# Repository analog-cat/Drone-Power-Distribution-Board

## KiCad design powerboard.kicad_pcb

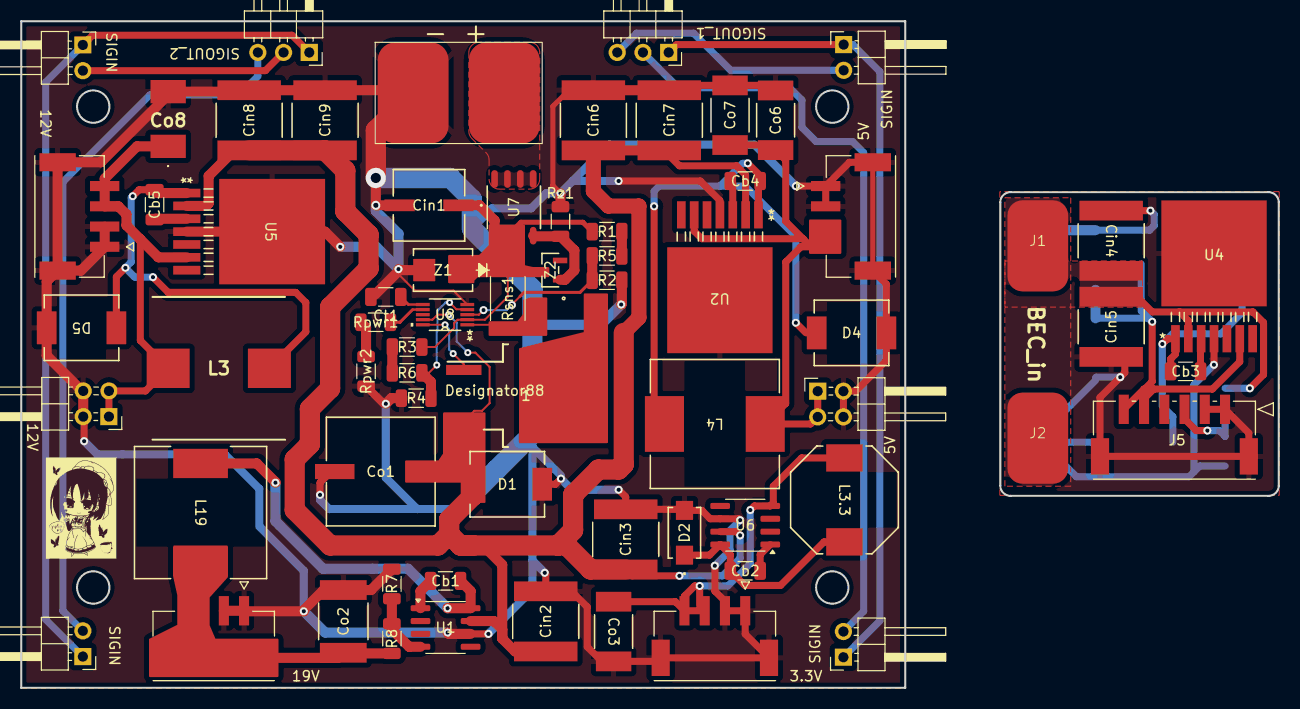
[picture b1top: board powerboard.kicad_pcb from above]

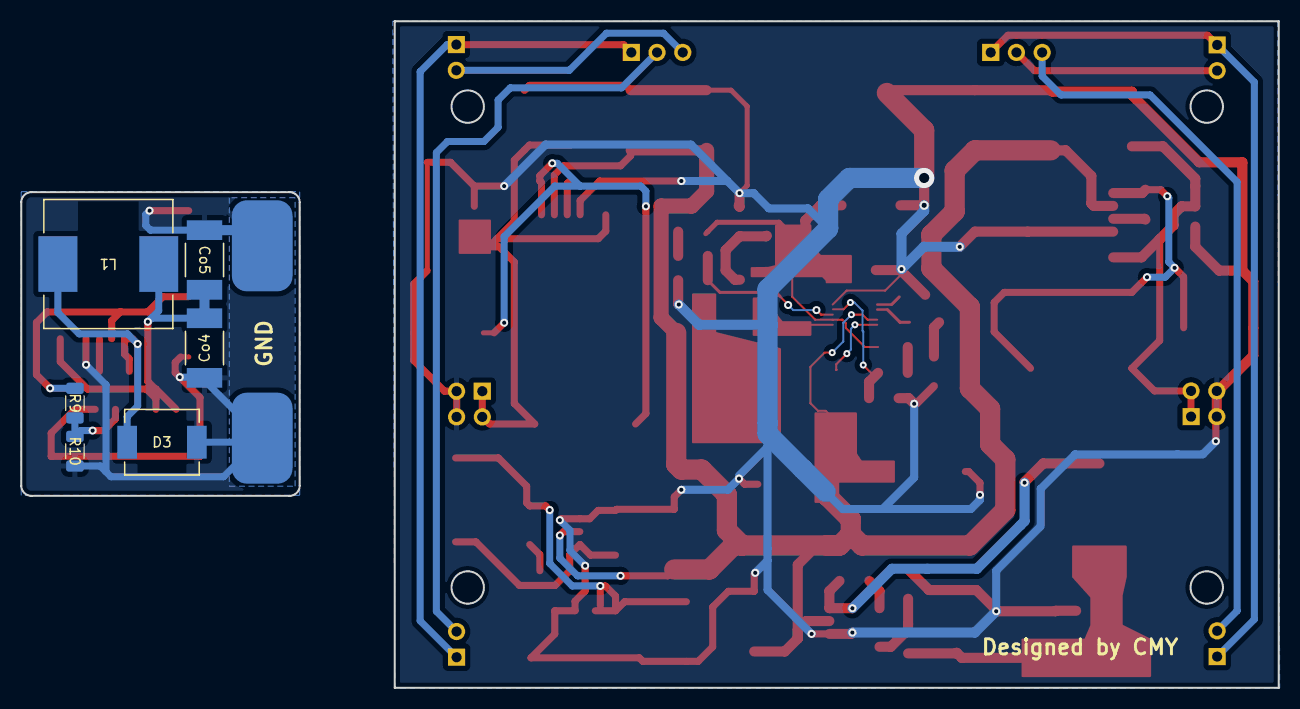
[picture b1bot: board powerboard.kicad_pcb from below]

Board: 2 copper layers, 124.2 x 65.8 mm, 73 parts (6 on the bottom side), 39 nets.

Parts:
1: CSD19536KTTT; KTT0002A
3.3V, 5V, 12V, 19V: 5024430470; MOLEX_5024430470
5V#2, 12V#2: Conn_01x04_Pin; PinHeader_2x02_P2.54mm_Horizontal
Cb1, Cb2, Cb3, Cb4, Cb5: 0.01u; C_1206_3216Metric
Cin1: 120u; CAP_ZKU_D8_PAN
Cin2, Cin3, Cin4, Cin5, Cin6, Cin7, Cin8, Cin9: 15u; CAP_594D-R_VSS
Co1: 330u; CAP_EEH_G_PAN
Co2: 33u; CAP_594D-D_VSS
Co3, Co4, Co5, Co6, Co7: 68u; CAP_594D-C_VSS
Co8: 100u; 594D107X9016C2T
Ct1: 150n; C_1206_3216Metric
D1: SS310; CR_SS310_TWS
D2: SS14; CR_SMA_403AE_OSI
D3, D4, D5: SK33; CR_SS310_TWS
J1, J2: Header2; BEC_io
J5: 5024430670; CON_5024430670
J12: Header2; Vin
L1, L4: DR125-330-R; DR125
L3: HC9-470-R; INDPM131141X750N
L3.3: 68u; IND_B82464G4_EPC
L19: 68u; IND_BOURNS_SRR1260
R1, R3: 36k; R_1206_3216Metric
R2: 8.2k; R_1206_3216Metric
R4: 4.02k; R_1206_3216Metric
R5, R6: 2k; R_1206_3216Metric
R7: 1k; R_1206_3216Metric
R8: 14.7k; R_1206_3216Metric
R9: 9.1M; R_1206_3216Metric
R10: 1M; R_1206_3216Metric
Rpwr1: 150k; R_1206_3216Metric
Rpwr2: 2k; R_1206_3216Metric
Rsns1: 6m; R_2512_6332Metric
Rz1: 1.8k; R_1206_3216Metric
SIGIN: Conn_01x02; PinHeader_1x02_P2.54mm_Horizontal
SIGIN#2, SIGIN#3, SIGIN#4: Conn_01x02; PinHeader_1x02_P2.54mm_Horizontal
SIGOUT_1, SIGOUT_2: Conn_01x03; PinHeader_1x03_P2.54mm_Horizontal
U1: LM2675M-ADJ; SOIC-8_3.9x4.9mm_P1.27mm
U2, U4: LM2676SX-5.0/NOPB; TS7B
U5: LM2676SX-12/NOPB; TS7B
U6: LM2675M-3.3; SOIC-8_3.9x4.9mm_P1.27mm
U7: FDS4435BZ; SO-8L-NB_FAS
U8: LM5069MM-2/NOPB; MUB10A
Z1: SMBJ30A; SMB_DIO
Z2: BZX84C12LT1G; SOT-23_ONS

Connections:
/1OUT: SIGIN.2, SIGOUT_1.2
/3OUT: SIGIN#3.2, SIGOUT_1.3
BEC_in: Cin4.1, Cin5.1, J1.1 (A), J2.1 (A), R9.1, U4.2 (IN)
GND: 3.3V.1, 3.3V.2, 3.3V.S1 (SHIELD1), 3.3V.S2 (SHIELD2), 5V.1, 5V.2, 5V.S1 (SHIELD1), 5V.S2 (SHIELD2), 5V#2.2, 5V#2.4, 12V.1, 12V.2, 12V.S1 (SHIELD1), 12V.S2 (SHIELD2), 12V#2.2, 12V#2.4, 19V.1, 19V.2, Cin1.2, Cin2.2, Cin3.2, Cin6.2, Cin7.2, Cin8.2, Cin9.2, Co1.2, Co2.2, Co3.2, Co6.2, Co7.2, Co8.2, Ct1.2, D1.2, D2.2 (A), D4.2 (A), D5.2 (A), J12.2 (B), R2.1, R4.1, R7.1, Rpwr2.1, Rz1.2, U1.6 (GND), U2.4 (GND), U2.8 (TAB), U5.4 (GND), U5.8 (TAB), U6.6 (GND), U8.5 (GND), Z1.2
GND_1: Cin4.2, Cin5.2, Co4.2, Co5.2, D3.2 (A), J1.2 (B), J2.2 (B), J5.1, J5.2, J5.7, J5.8, R10.2, U4.4 (GND), U4.8 (TAB)
unnamed: 1.2 (Drain), Rsns1.2, U8.1 (SEN)
unnamed: 1.1 (Gate), U8.10 (GATE)
unnamed: SIGIN.1, SIGIN#3.1, SIGOUT_1.1
unnamed: Cb2.2, D2.1 (K), L3.3.2, U6.8 (VSW)
unnamed: Cb3.1, D3.1 (K), L1.2, U4.1 (SW)
unnamed: Cb4.1, D4.1 (K), L4.2, U2.1 (SW)
unnamed: Cb5.1, D5.1 (K), L3.2, U5.1 (SW)
unnamed: SIGIN#4.2, SIGOUT_2.3
unnamed: SIGIN#2.1, SIGIN#4.1, SIGOUT_2.1
unnamed: SIGIN#2.2, SIGOUT_2.2
unnamed: R1.1, R5.2
unnamed: R3.1, R6.2
unnamed: Rpwr1.1, Rpwr2.2
unnamed: Cb1.1, U1.1 (CB)
unnamed: R7.2, R8.1, U1.4 (FB)
unnamed: Cb1.2, L19.1, U1.8 (VSW)
unnamed: Cb4.2, U2.3 (CB)
unnamed: Cb3.2, U4.3 (CB)
unnamed: Cb5.2, U5.3 (CB)
unnamed: Cb2.1, U6.1 (CB)
unnamed: Rz1.1, U7.4 (G), Z2.1 (ANODE)
unnamed: R4.2, R6.1, U8.4 (OVLO)
unnamed: Rpwr1.2, U8.7 (PWR)
unnamed: Ct1.1, U8.6 (TIMER)
unnamed: R2.2, R5.1, U8.3 (UVLO)
V_3.3: 3.3V.3, 3.3V.4, Co3.1, L3.3.1, U6.4 (FB)
V_5_1: Co4.1, Co5.1, J5.5, J5.6, L1.1, U4.6 (FB)
V_5_2: 5V.3, 5V.4, 5V#2.1, 5V#2.3, Co6.1, Co7.1, L4.1, U2.6 (FB)
V_12: 12V.3, 12V.4, 12V#2.1, 12V#2.3, Co8.1, L3.1, U5.6 (FB)
V_19: 19V.3, 19V.4, 19V.S1 (SHIELD1), 19V.S2 (SHIELD2), Co2.1, L19.2, R8.2
V_out_1: Cin1.1, R1.2, R3.2, Rsns1.1, U7.1 (S), U7.2 (S), U7.3 (S), U8.2 (VIN), Z1.1, Z2.3 (CATHODE)
V_out_2: 1.3 (Source), Cin2.1, Cin3.1, Cin6.1, Cin7.1, Cin8.1, Cin9.1, Co1.1, D1.1, U1.7 (VIN), U2.2 (IN), U5.2 (IN), U6.7 (VIN), U8.9 (OUT)
Vin: J12.1 (A), U7.5 (D), U7.6 (D), U7.7 (D), U7.8 (D)
batt_v_sns: J5.3, R9.2, R10.1
